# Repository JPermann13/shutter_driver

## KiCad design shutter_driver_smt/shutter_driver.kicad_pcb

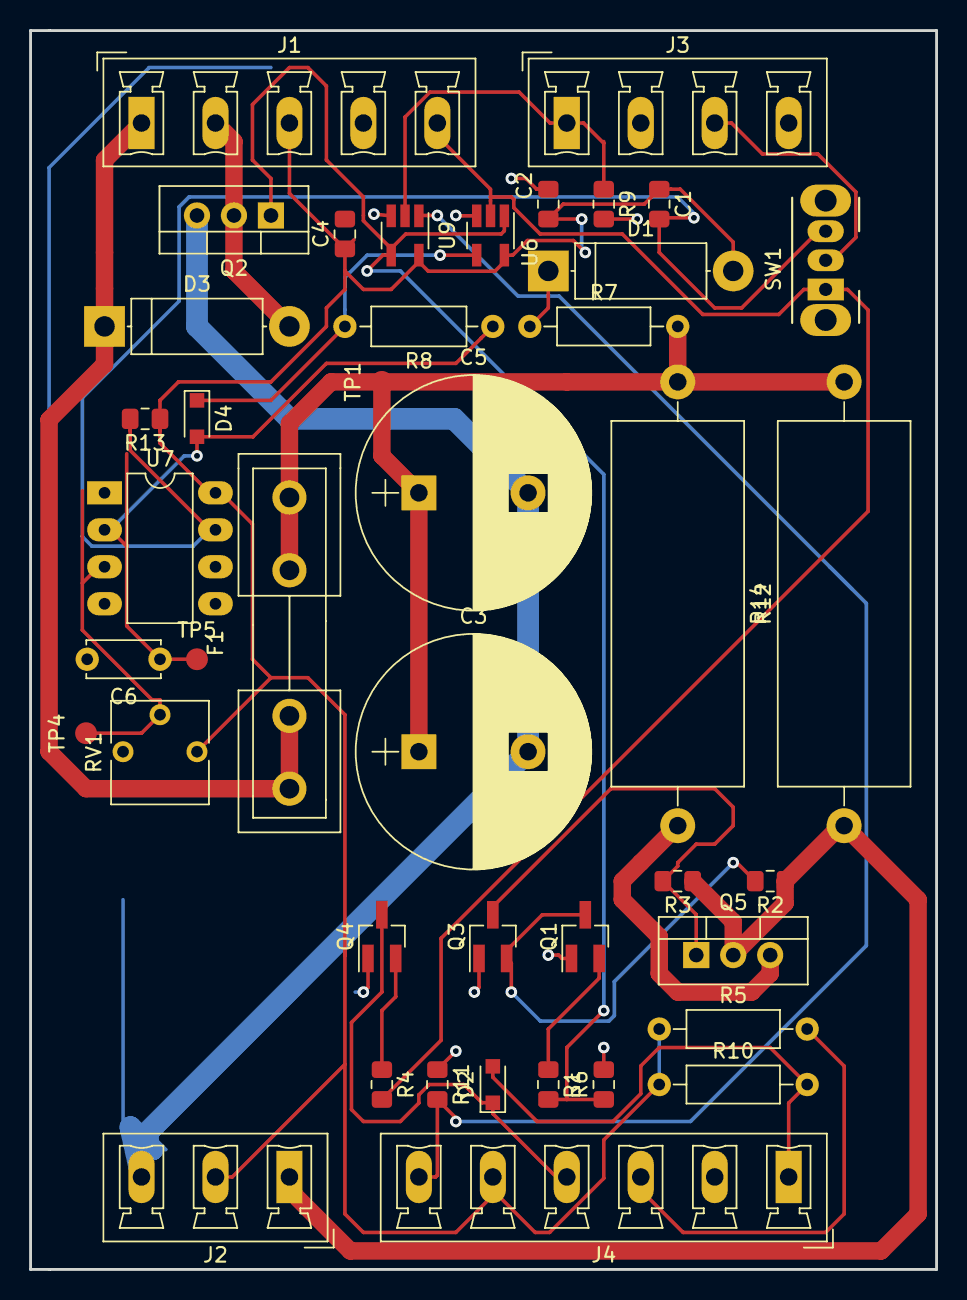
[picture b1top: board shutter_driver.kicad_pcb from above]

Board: 2 copper layers, 62.2 x 85.1 mm, 42 parts (0 on the bottom side), 24 nets.

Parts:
C1: 1n; C_0805_2012Metric_Pad1.15x1.40mm_HandSolder
C2, C4: .1u; C_0805_2012Metric_Pad1.15x1.40mm_HandSolder
C3, C5: 2200uF; CP_Radial_D16.0mm_P7.50mm
C6: 1u; C_Disc_D5.0mm_W2.5mm_P5.00mm
D1, D3: N4001; D_5W_P12.70mm_Horizontal
D2, D4: 1N914; D_SOD-323_HandSoldering
F1: Fuse; Fuseholder5x20_horiz_open_inline_Type-I
J1: SHUTTER; PhoenixContact_MCV-G_05x5.08mm_Vertical
J2: POWER; PhoenixContact_MCV-G_03x5.08mm_Vertical
J3: I/O; PhoenixContact_MCV-G_04x5.08mm_Vertical
J4: FRONT; PhoenixContact_MCV-G_06x5.08mm_Vertical
Q1, Q3, Q4: 2N3904; SOT-23_Handsoldering
Q2: FQP30N06L-ND; TO-220-3_Vertical
Q5: Q_PMOS_GDS; TO-220-3_Vertical
R1, R2, R3, R6, R9, R13: 10k; R_0805_2012Metric_Pad1.15x1.40mm_HandSolder
R4: 4.7k; R_0805_2012Metric_Pad1.15x1.40mm_HandSolder
R5, R10: 220; R_Axial_DIN0207_L6.3mm_D2.5mm_P10.16mm_Horizontal
R7: 5; R_Axial_DIN0207_L6.3mm_D2.5mm_P10.16mm_Horizontal
R8: 50k; R_Axial_DIN0207_L6.3mm_D2.5mm_P10.16mm_Horizontal
R11: 10K; R_0805_2012Metric_Pad1.15x1.40mm_HandSolder
R12, R14: 50; R_Axial_Power_L25.0mm_W9.0mm_P30.48mm
RV1: 10k; Potentiometer_Trimmer_Vishay_T73YP_Horizontal
SW1: SW_DPDT_x2; SW_CuK_OS102011MA1QN1_SPDT_Angled
TP1: CAP_SHORT; Measurement_Point_Round-SMD-Pad_Small
TP4: V_trig; Measurement_Point_Round-SMD-Pad_Small
TP5: V_RC; Measurement_Point_Round-SMD-Pad_Small
U6, U9: SN74LVC1G86; SOT-23-5_HandSoldering
U7: LM311; DIP-8_W7.62mm_LongPads

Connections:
+5V: C1.1, C2.1, C4.1, D1.2, J1.3, J2.2, J4.5, R5.1, R10.1, R13.1, RV1.1, U6.5, U7.8, U9.5
+24V: J2.1, Q5.2, R2.1, R3.1, R12.1
/CAP_POWER: C3.1, C5.1, F1.2, R7.2, R12.2, R14.1, TP1.1
/LED_G+: D2.2, J4.1, R10.2
/LED_R+: J4.3, R5.2
/LED_R-: D2.1, J4.4, Q4.3
/OUT_TO_COMP: J3.3, SW1.2
/SHUTTER_HI: D3.1, F1.1, J1.1
/SHUTTER_LOW: D3.2, J1.2, Q2.2
/SHUTTER_RET: J1.5, R4.2, SW1.1, U6.2
/SIG: Q2.1, R1.2, R6.1, U6.1, U9.4
/SIG_IN: J3.1, R9.1, U9.2
GND: C2.2, C3.2, C4.2, C5.2, C6.2, J1.4, J2.3, J3.2, J3.4, J4.2, Q1.1, Q2.3, Q3.1, Q4.1, R6.2, R9.2, R11.1, RV1.3, U6.3, U7.1, U7.4, U9.3
unnamed: C1.2, R13.2, SW1.3, U7.7
unnamed: C6.1, D4.2, R8.1, TP5.1, U7.2
unnamed: D1.1, R7.1
unnamed: D4.1, R8.2, U6.4
unnamed: J4.6, R11.2, U9.1
unnamed: Q1.2, R1.1
unnamed: Q1.3, Q3.2, R2.2
unnamed: Q3.3, Q5.1, R3.2
unnamed: Q4.2, R4.1
unnamed: Q5.3, R14.2
unnamed: RV1.2, TP4.1, U7.3

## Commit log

2019-04-23 brach test
2019-04-23 simplified schamatic for poster.
2019-04-25 spelling interrupt
2019-05-22 fixed backward pmos
2019-05-22 minor fixes including filter caps on rails of gates and comparator. note PMOS flipped in last commit.
2019-05-22 redid file orgnization
2019-05-22 added bypass for gate
2019-12-19 adds psoc
2019-12-24 adds v2 as of 12.20
2019-12-24 adds kicad init
2019-12-24 adds timer interrrupt
2019-12-24 adds schamatic of basic circuit in kicad
2020-01-14 Add files via upload
    Updated kicad schematic
